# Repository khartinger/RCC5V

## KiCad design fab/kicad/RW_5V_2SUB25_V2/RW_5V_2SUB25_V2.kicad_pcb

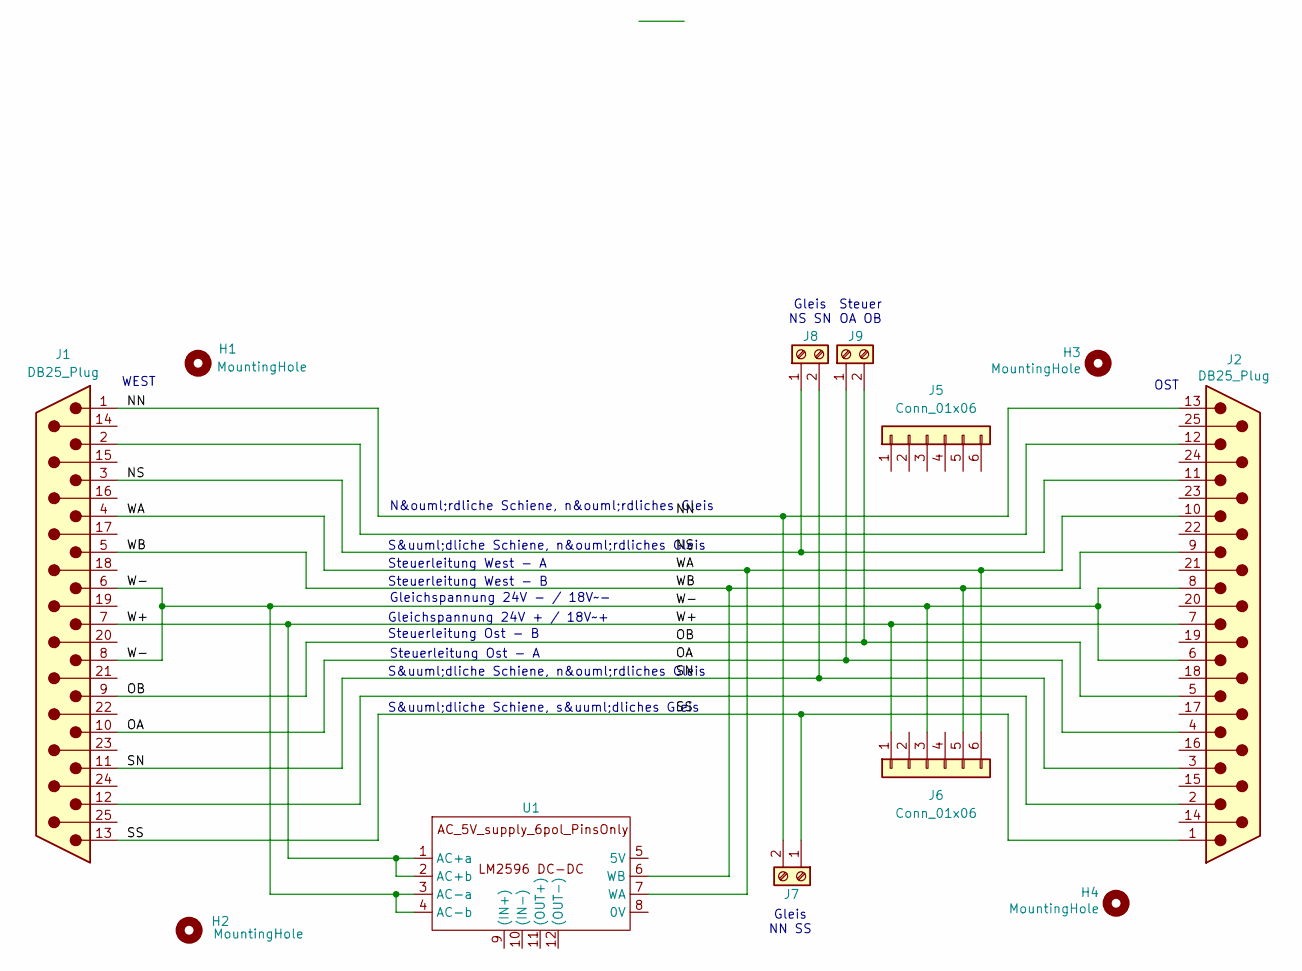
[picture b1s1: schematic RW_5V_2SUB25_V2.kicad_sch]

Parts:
H1, H2, H3, H4: MountingHole; MountingHole_2.7mm_M2.5_DIN965_Pad_TopBottom
J1, J2: DB25_Plug; DSUB-25_Male_Horizontal_P2.77x2.84mm_EdgePinOffset7.70mm_Ho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
J5, J6: Conn_01x06; PinSocket_1x06_P2.54mm_Vertical_kh
J7, J8, J9: Screw_Terminal_01x02_P5
U1: AC_5V_supply_6pol_PinsOnly

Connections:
/NN: J1.1, J2.13, J7.2
/NS: J1.3, J2.11, J8.1
/OA: J1.10, J2.4, J9.1
/OB: J1.9, J2.5, J9.2
/SN: J1.11, J2.3, J8.2
/SS: J1.13, J2.1, J7.1
/W+: J1.7, J2.7, J6.1, U1.1 (AC+a), U1.2 (AC+b)
/W-: J1.6, J1.8, J2.6, J2.8, J6.3, U1.3 (AC-a), U1.4 (AC-b)
/WA: J1.4, J2.10, J6.6, U1.7 (WA)
/WB: J1.5, J2.9, J6.5, U1.6 (WB)
unnamed: J1.2, J2.12
unnamed: J1.12, J2.2

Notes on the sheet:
Gleis NS SN
S&uuml;dliche Schiene, s&uuml;dliches Gleis
S&uuml;dliche Schiene, n&ouml;rdliches Gleis
Steuer OA OB
Gleichspannung 24V - / 18V~-
N&ouml;rdliche Schiene, n&ouml;rdliches Gleis
Steuerleitung West - A
Steuerleitung Ost - B
Steuerleitung West - B
WEST
Gleichspannung 24V + / 18V~+
OST
Gleis NN SS
Steuerleitung Ost - A

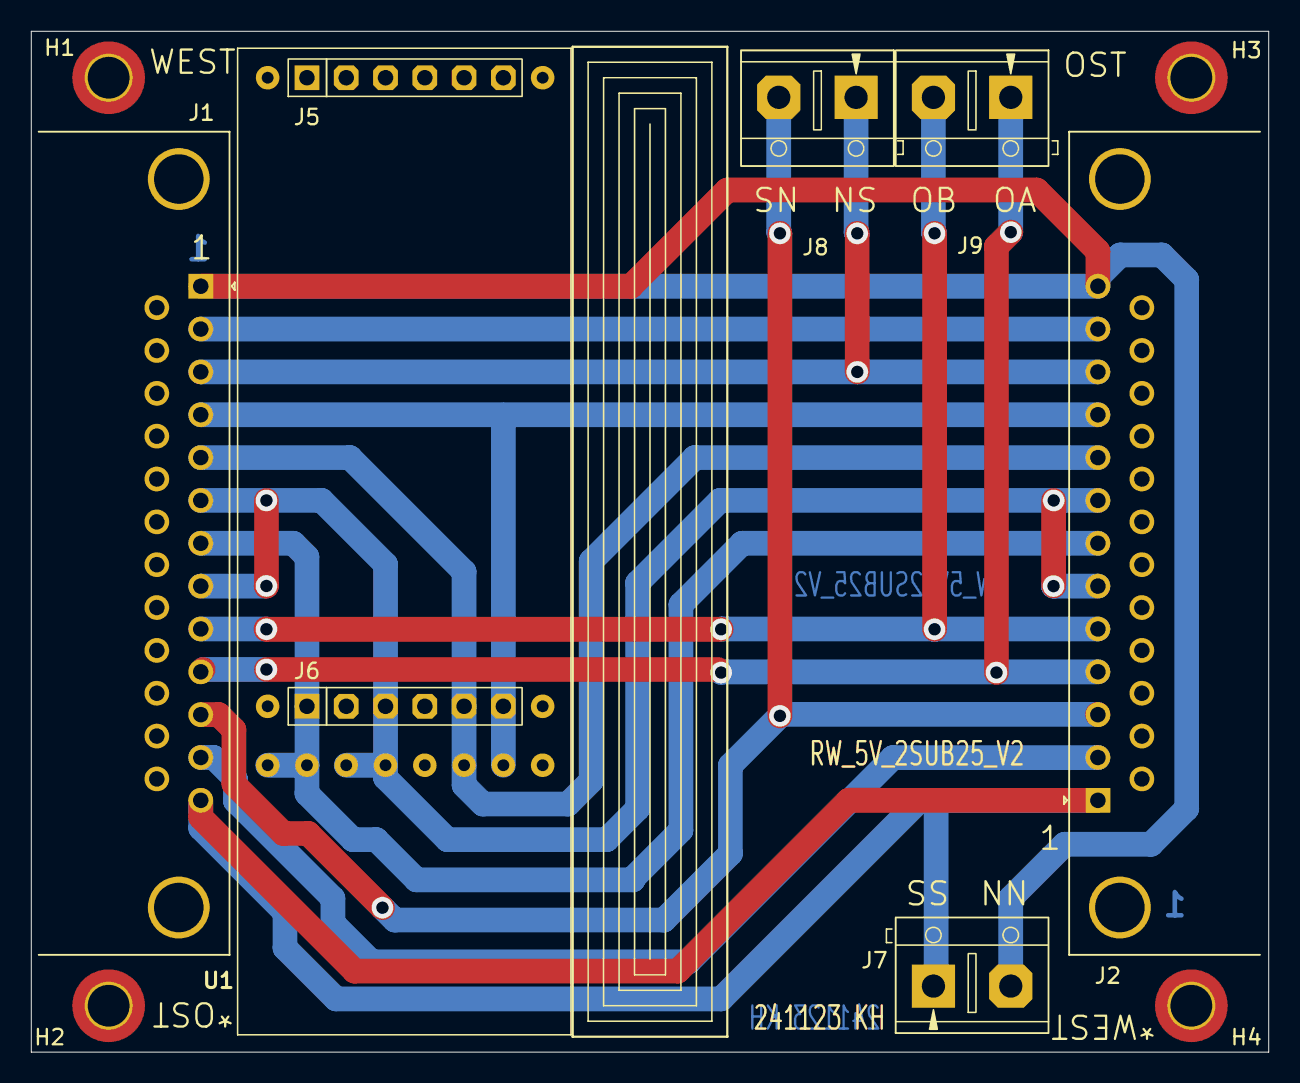
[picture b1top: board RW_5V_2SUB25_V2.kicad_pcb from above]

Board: 2 copper layers, 80.0 x 66.0 mm, 12 parts (0 on the bottom side), 12 nets.

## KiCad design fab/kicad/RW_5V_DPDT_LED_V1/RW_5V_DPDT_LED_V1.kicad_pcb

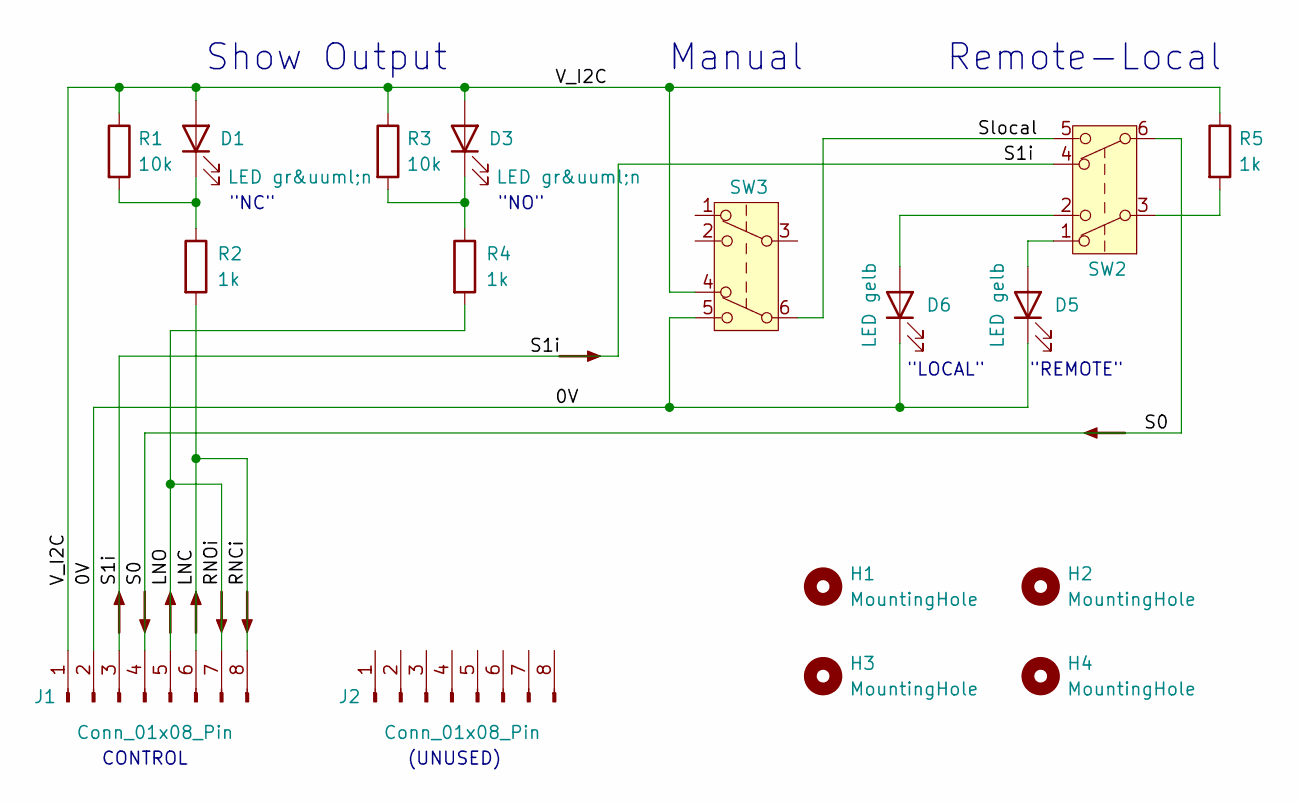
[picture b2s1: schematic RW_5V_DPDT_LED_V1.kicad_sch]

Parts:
D1, D3: LED gr&uuml;n; LED_D3.0mm
D5, D6: LED gelb; LED_D3.0mm
H1, H2, H3, H4: MountingHole; MountingHole_2.2mm_M2_Pad_TopBottom_kh
J1, J2: Conn_01x08_Pin; PinSocket_1x08_P2.54mm_Vertical_11mm_kh
R1, R3: 10k; R_Axial_DIN0204_L3.6mm_D1.6mm_P2.54mm_Vertical
R2, R4: 1k; R_Axial_DIN0207_L6.3mm_D2.5mm_P15.24mm_Horizontal_kh
R5: 1k; R_Axial_DIN0204_L3.6mm_D1.6mm_P2.54mm_Vertical
SW2, SW3: SW_Push_DPDT_8x8

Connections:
/0V: D5.1 (K), D6.1 (K), J1.2, SW3.5 (B)
/LNC: J1.6, J1.8, R2.2
/LNO: J1.5, J1.7, R4.2
/S0: J1.4, SW2.6 (C)
/S1i: J1.3, SW2.4 (A)
/Slocal: SW2.5 (B), SW3.6 (C)
/V_I2C: D1.2 (A), D3.2 (A), J1.1, R1.1, R3.1, R5.1, SW3.4 (A)
unnamed: D1.1 (K), R1.2, R2.1
unnamed: D3.1 (K), R3.2, R4.1
unnamed: D5.2 (A), SW2.1 (A)
unnamed: D6.2 (A), SW2.2 (B)
unnamed: R5.2, SW2.3 (C)

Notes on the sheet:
(UNUSED)
"LOCAL"
Manual
"REMOTE"
Remote-Local
CONTROL
Show Output
"NC"
"NO"

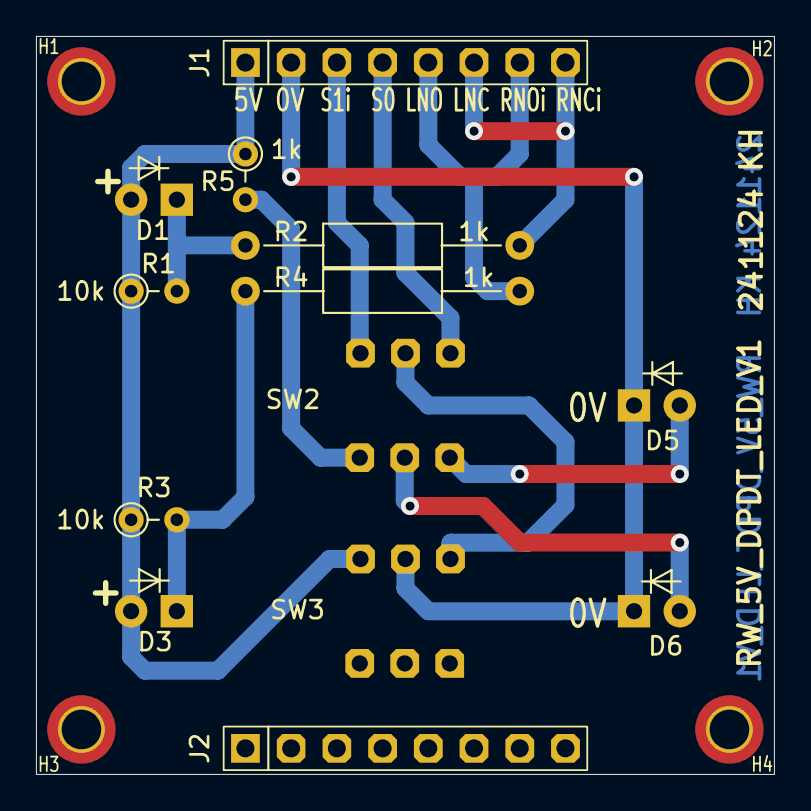
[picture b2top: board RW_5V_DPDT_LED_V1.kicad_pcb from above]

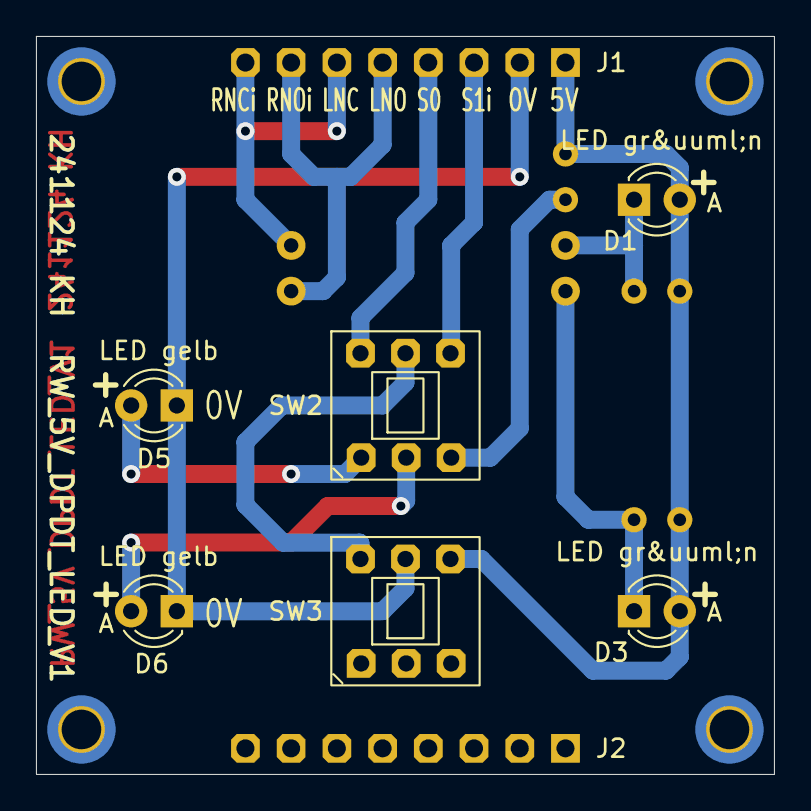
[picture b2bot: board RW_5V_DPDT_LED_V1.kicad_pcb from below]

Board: 2 copper layers, 41.0 x 41.0 mm, 17 parts (6 on the bottom side), 12 nets.

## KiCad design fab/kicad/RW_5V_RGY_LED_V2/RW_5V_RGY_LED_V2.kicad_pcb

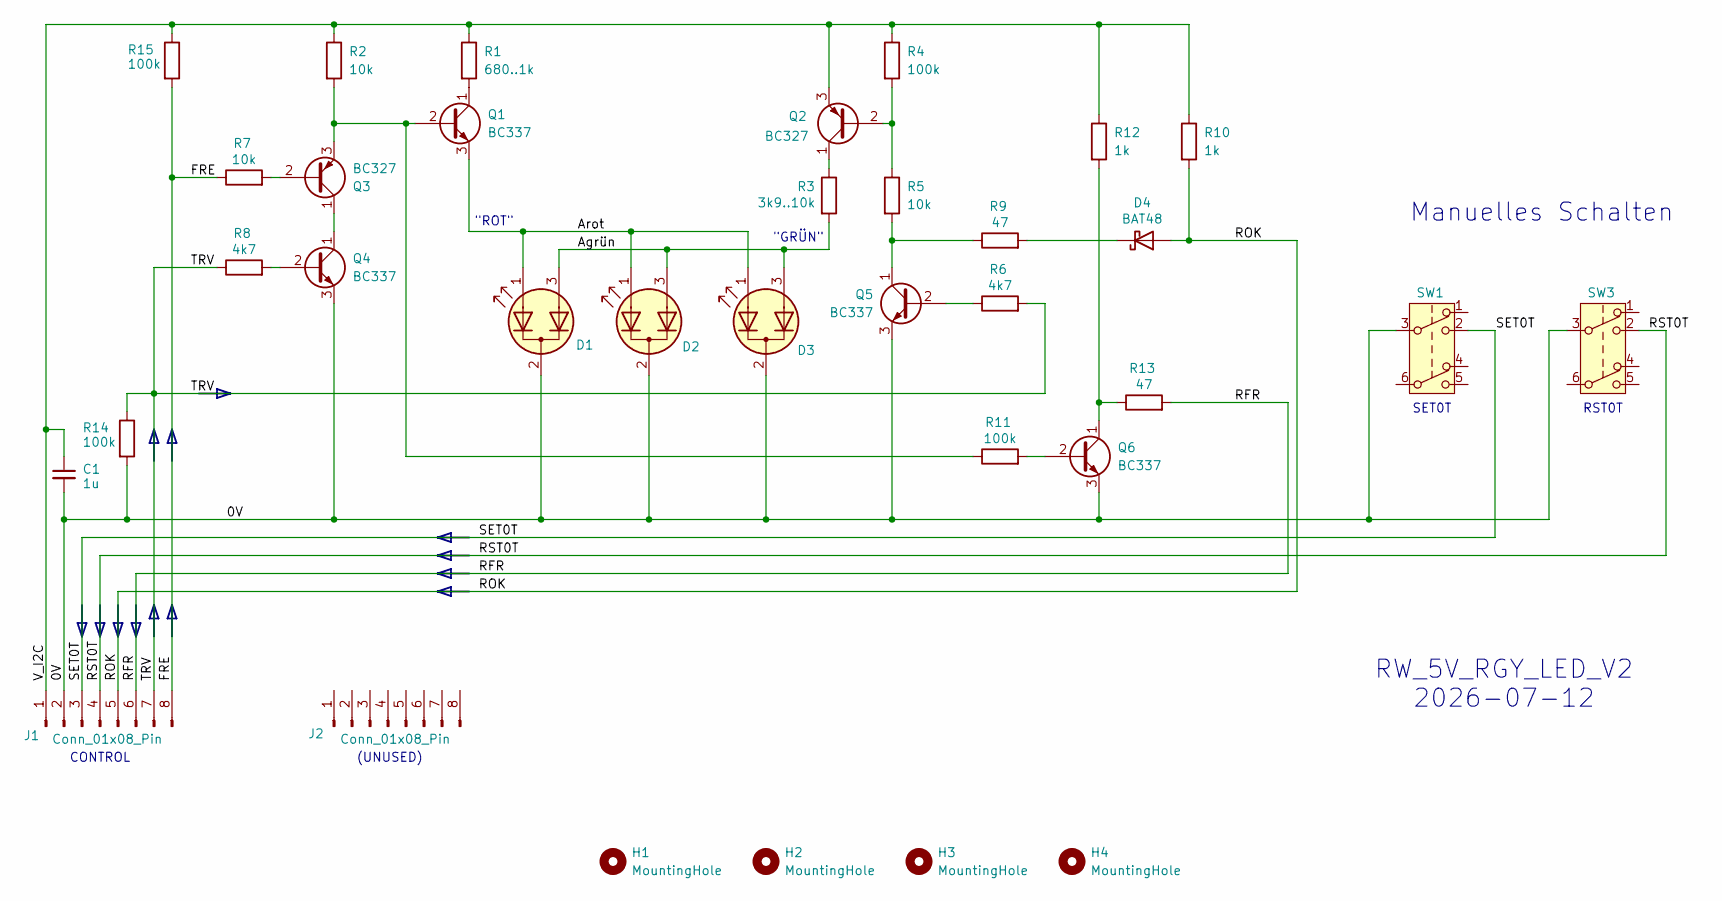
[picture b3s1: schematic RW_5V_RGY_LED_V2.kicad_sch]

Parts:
C1: 1u; C_L4mm_D3mm_P2.54mm_kh
D1, D2, D3: LED_Dual_AKA; LED_D5.0mm-3
D4: BAT48; D_DO-35_SOD27_P2.54mm_Vertical_AnodeUp
H1, H2, H3, H4: MountingHole; MountingHole_2.2mm_M2_Pad_TopBottom_kh
J1, J2: Conn_01x08_Pin; PinSocket_1x08_P2.54mm_Vertical_11mm_kh
Q1, Q4, Q5, Q6: BC337; TO-92_Inline_Wide_custom
Q2, Q3: BC327; TO-92_Inline_Wide_custom
R1: 680..1k; R_Axial_DIN0204_L3.6mm_D1.6mm_P7.62mm_Horizontal
R2, R5: 10k; R_Axial_DIN0204_L3.6mm_D1.6mm_P2.54mm_Vertical_kh
R3: 3k9..10k; R_Axial_DIN0204_L3.6mm_D1.6mm_P2.54mm_Vertical_kh
R4, R14, R15: 100k; R_Axial_DIN0204_L3.6mm_D1.6mm_P2.54mm_Vertical
R6, R8: 4k7; R_Axial_DIN0204_L3.6mm_D1.6mm_P2.54mm_Vertical_kh
R7: 10k; R_Axial_DIN0204_L3.6mm_D1.6mm_P3.81mm_Vertical_kh
R9: 47; R_Axial_DIN0204_L3.6mm_D1.6mm_P2.54mm_Vertical_kh
R10, R12: 1k; R_Axial_DIN0204_L3.6mm_D1.6mm_P2.54mm_Vertical_kh
R11: 100k; R_Axial_DIN0204_L3.6mm_D1.6mm_P7.62mm_Horizontal
R13: 47; R_Axial_DIN0204_L3.6mm_D1.6mm_P7.62mm_Horizontal
SW1, SW3: SW_Push_DPDT_8x8

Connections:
/0V: C1.2, D1.2 (K), D2.2 (K), D3.2 (K), J1.2, Q4.3 (E), Q5.3 (E), Q6.3 (E), R14.2, SW1.3 (C), SW3.3 (C)
/Agrün: D1.3 (A2), D2.3 (A2), D3.3 (A2), R3.2
/Arot: D1.1 (A1), D2.1 (A1), D3.1 (A1), Q1.3 (E)
/FRE: J1.8, R7.1, R15.2
/RFR: J1.6, R13.2
/ROK: D4.2 (A), J1.5, R10.2
/RST0T: J1.4, SW3.2 (B)
/SET0T: J1.3, SW1.2 (B)
/TRV: J1.7, R6.2, R8.1, R14.1
/V_I2C: C1.1, J1.1, Q2.3 (E), R1.1, R2.1, R4.1, R10.1, R12.1, R15.1
unnamed: D4.1 (K), R9.2
unnamed: Q1.2 (B), Q3.3 (E), R2.2, R11.1
unnamed: Q1.1 (C), R1.2
unnamed: Q2.2 (B), R4.2, R5.1
unnamed: Q2.1 (C), R3.1
unnamed: Q3.2 (B), R7.2
unnamed: Q3.1 (C), Q4.1 (C)
unnamed: Q4.2 (B), R8.2
unnamed: Q5.2 (B), R6.1
unnamed: Q5.1 (C), R5.2, R9.1
unnamed: Q6.2 (B), R11.2
unnamed: Q6.1 (C), R12.2, R13.1

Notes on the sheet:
(UNUSED)
SET0T
Manuelles Schalten
"GRÜN"
RW_5V_RGY_LED_V2 2026-07-12
CONTROL
"ROT"
RST0T

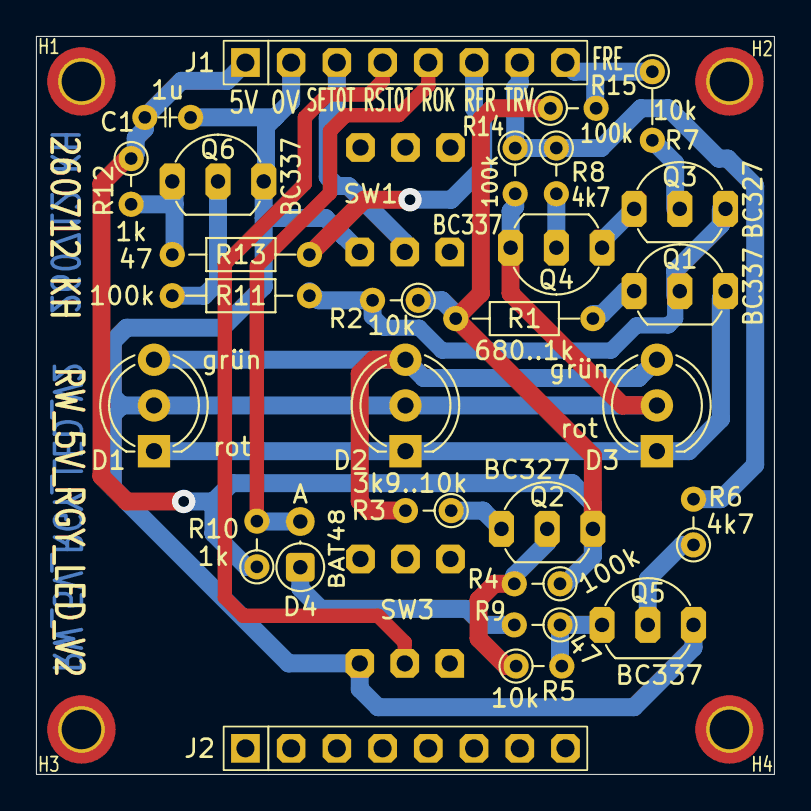
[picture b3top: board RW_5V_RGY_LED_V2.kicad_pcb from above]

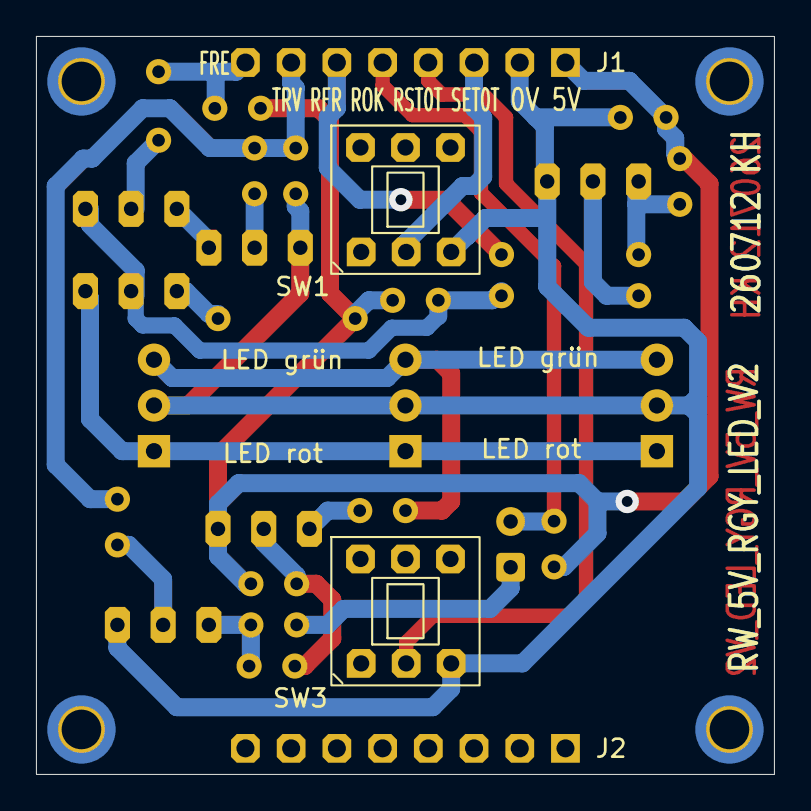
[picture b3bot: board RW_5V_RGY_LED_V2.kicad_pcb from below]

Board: 2 copper layers, 41.0 x 41.0 mm, 34 parts (2 on the bottom side), 22 nets.

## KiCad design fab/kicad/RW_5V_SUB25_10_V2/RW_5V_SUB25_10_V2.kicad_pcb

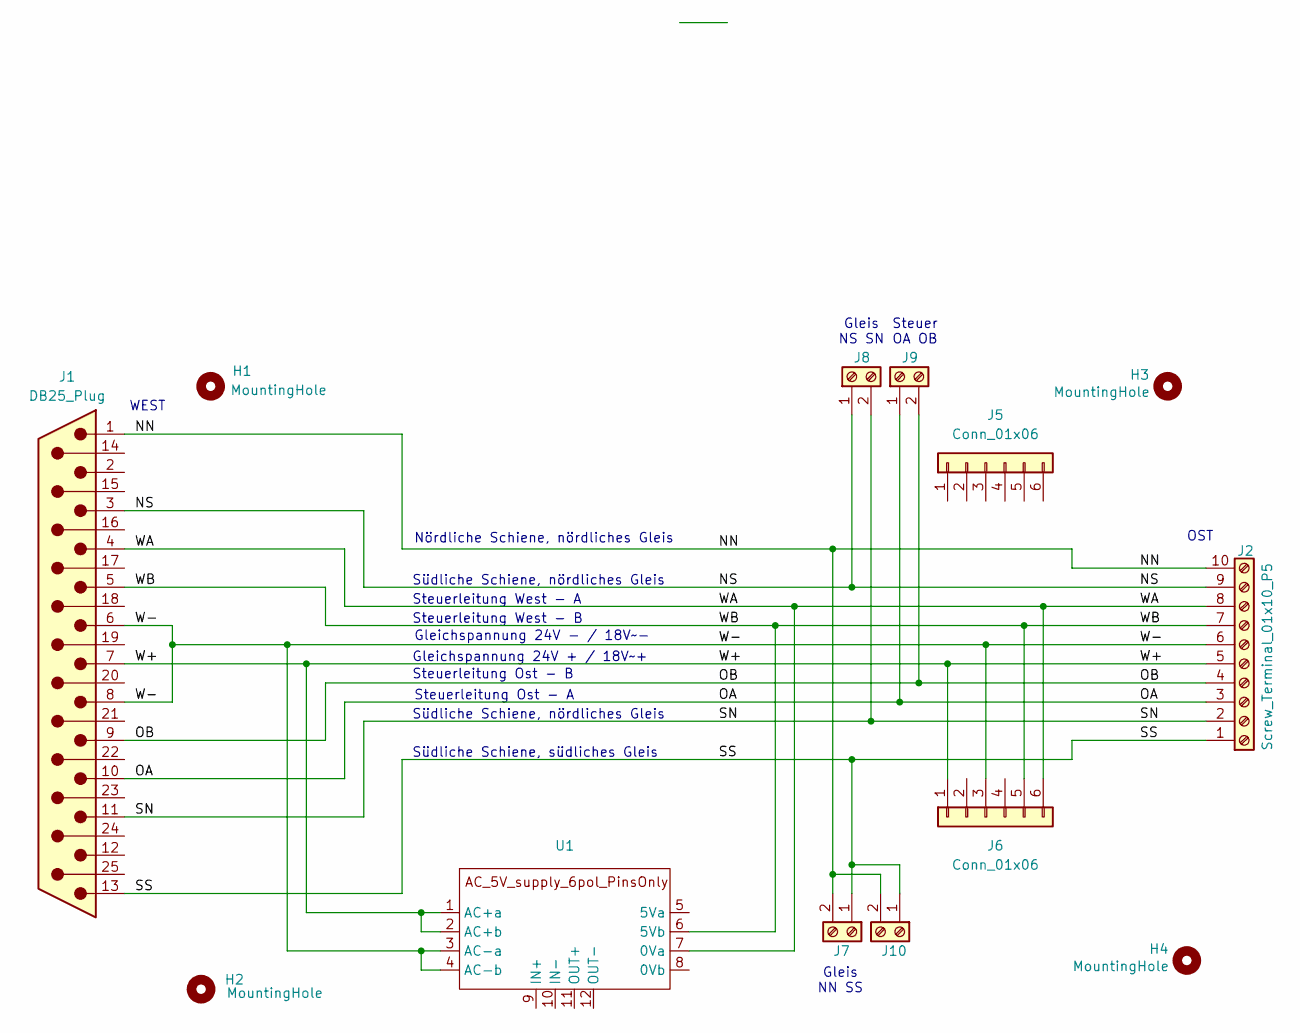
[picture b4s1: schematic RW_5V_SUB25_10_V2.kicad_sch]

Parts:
H1, H2, H3, H4: MountingHole; MountingHole_2.7mm_M2.5_DIN965_Pad_TopBottom
J1: DB25_Plug; DSUB-25_Male_Horizontal_P2.77x2.84mm_EdgePinOffset7.70mm_Ho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
J2: Screw_Terminal_01x10_P5
J5, J6: Conn_01x06; PinSocket_1x06_P2.54mm_Vertical_kh
J7, J8, J9, J10: Screw_Terminal_01x02_P5
U1: AC_5V_supply_6pol_PinsOnly

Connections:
/NN: J1.1, J2.10, J7.2, J10.2
/NS: J1.3, J2.9, J8.1
/OA: J1.10, J2.3, J9.1
/OB: J1.9, J2.4, J9.2
/SN: J1.11, J2.2, J8.2
/SS: J1.13, J2.1, J7.1, J10.1
/W+: J1.7, J2.5, J6.1, U1.1 (AC+a), U1.2 (AC+b)
/W-: J1.6, J1.8, J2.6, J6.3, U1.3 (AC-a), U1.4 (AC-b)
/WA: J1.4, J2.8, J6.6, U1.7 (0Va)
/WB: J1.5, J2.7, J6.5, U1.6 (5Vb)

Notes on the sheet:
Gleis NS SN
Südliche Schiene, südliches Gleis
Südliche Schiene, nördliches Gleis
Steuer OA OB
Gleichspannung 24V - / 18V~-
Nördliche Schiene, nördliches Gleis
Steuerleitung West - A
Steuerleitung Ost - B
Steuerleitung West - B
WEST
Gleichspannung 24V + / 18V~+
OST
Gleis NN SS
Steuerleitung Ost - A

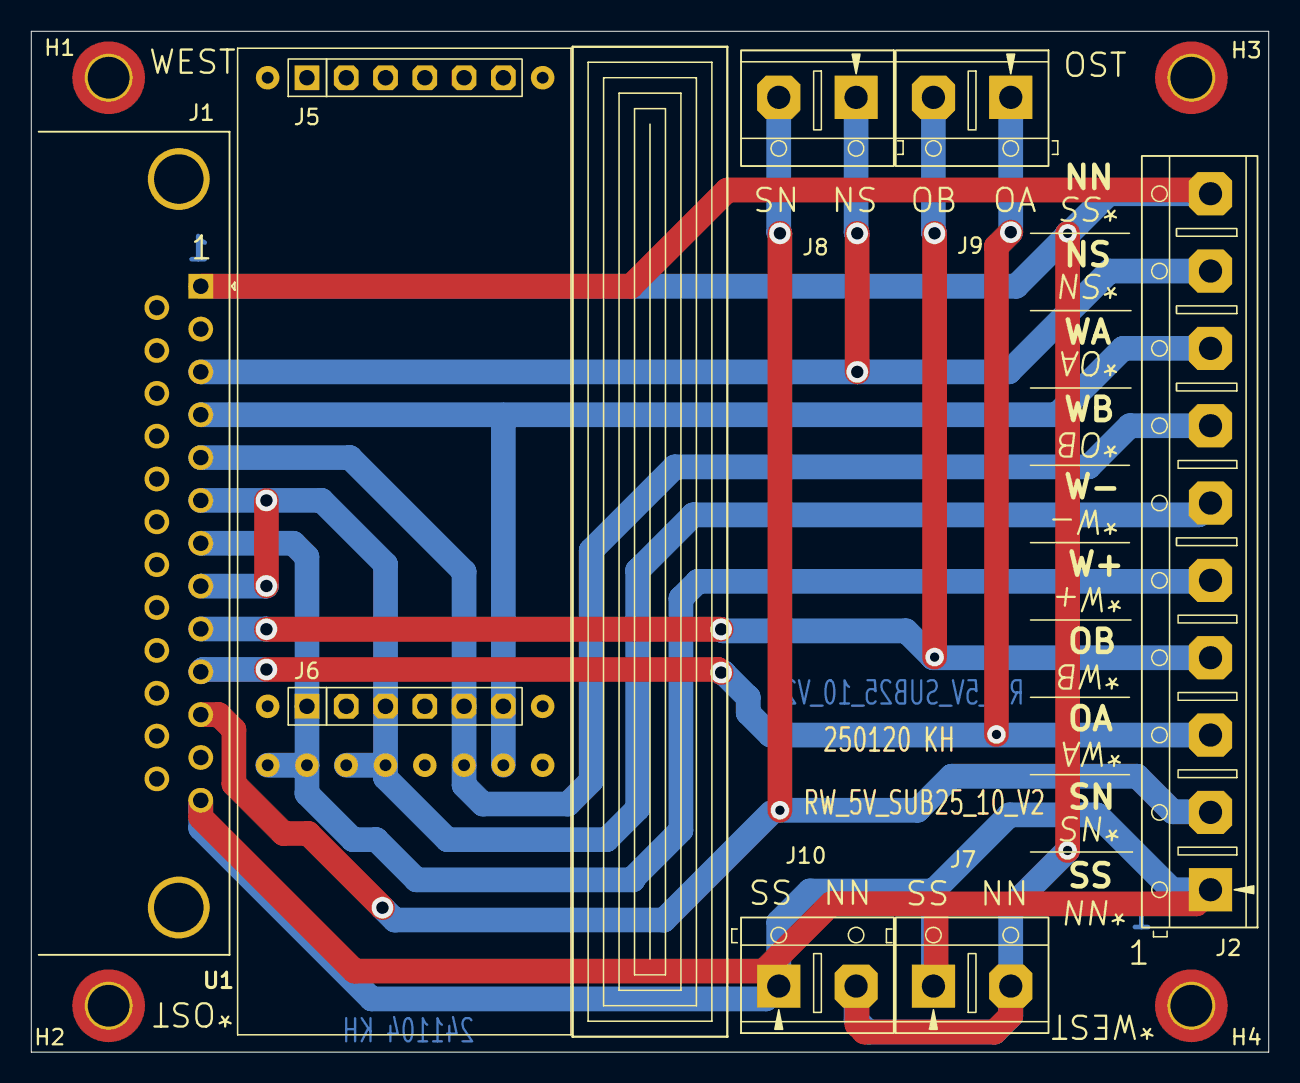
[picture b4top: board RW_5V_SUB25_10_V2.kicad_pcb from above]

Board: 2 copper layers, 80.0 x 66.0 mm, 13 parts (0 on the bottom side), 10 nets.
